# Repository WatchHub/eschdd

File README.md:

BLDC Motor Controller Circuit by youtube user: https://www.youtube.com/channel/UCetsjYU0iBuMPbXi1aA_XXg

Demo: https://www.youtube.com/watch?v=p9SYtOp8aG0

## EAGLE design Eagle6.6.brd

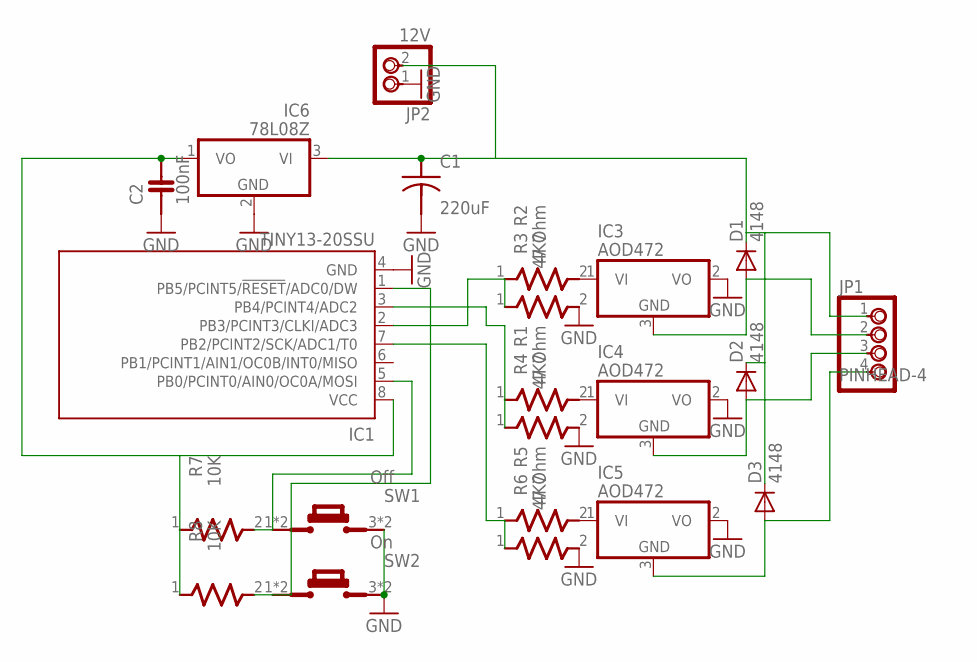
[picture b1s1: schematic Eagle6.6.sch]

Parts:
C1: 220uF; CAP-2,5
C2: 100nF; CAP-NP5
D1, D2, D3: 4148; SMB
IC1: TINY13-20SSU; 8S1
IC3, IC4, IC5: AOD472; TO252
IC6: 78L08Z; TO92
JP1: PINHEAD-4
JP2: 12V; PINHEAD-2
R1, R2, R5: 47 Ohm; R-7,5
R3, R4, R6: 4K7; R-7,5
R7, R8: 10K; R-7,5
SW1: Off; KEY-5
SW2: On; KEY-5

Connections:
GND: C1.- (2), C2.1, IC1.4 (GND), IC3.2 (VO), IC4.2 (VO), IC5.2 (VO), IC6.2 (GND), JP2.1, R3.2, R4.2, R6.2, SW1.3 (2), SW1.4 (2), SW2.3 (2), SW2.4 (2)
unnamed: IC3.1 (VI), R2.2
unnamed: IC4.1 (VI), R1.2
unnamed: IC5.1 (VI), R5.2
unnamed: IC1.7 (PB2/PCINT2/SCK/ADC1/T0), R5.1, R6.1
unnamed: IC1.3 (PB4/PCINT4/ADC2), R1.1, R4.1
unnamed: IC1.2 (PB3/PCINT3/CLKI/ADC3), R2.1, R3.1
unnamed: IC1.5 (PB0/PCINT0/AIN0/OC0A/MOSI), R7.2, SW1.1, SW1.2 (1)
unnamed: D1.A, IC3.3 (GND), JP1.2
unnamed: D2.A, IC4.3 (GND), JP1.3
unnamed: D3.A, IC5.3 (GND), JP1.4
unnamed: C1.+ (1), D1.C, D2.C, D3.C, IC6.3 (VI), JP1.1, JP2.2
unnamed: IC1.1 (PB5/PCINT5/!RESET!/ADC0/DW), R8.2, SW2.1, SW2.2 (1)
unnamed: C2.2, IC1.8 (VCC), IC6.1 (VO), R7.1, R8.1

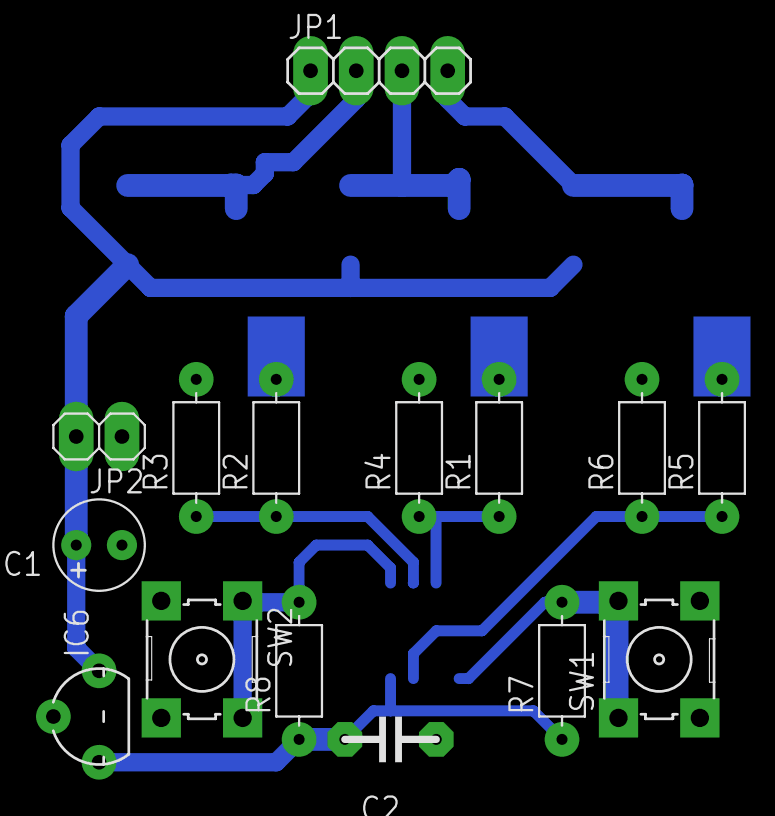
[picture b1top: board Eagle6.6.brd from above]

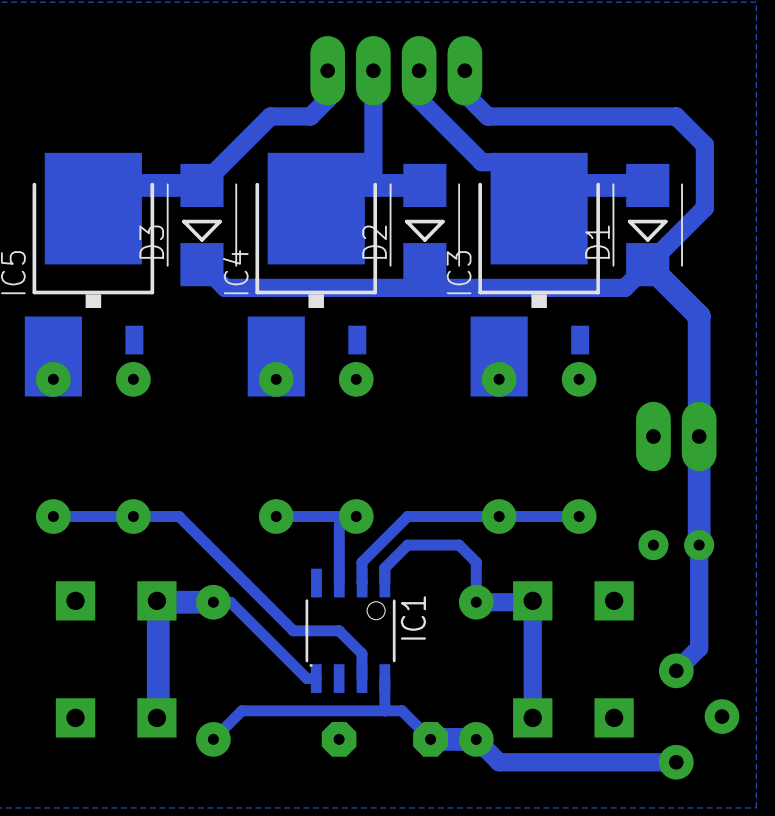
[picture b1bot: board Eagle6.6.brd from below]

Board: 2 copper layers, 22 parts (7 on the bottom side), 14 nets.

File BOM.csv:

"Part";"Value";"Device";"Package";"Description";"MF";"MPN";"OC_FARNELL";"OC_NEWARK";
"C1";"220uF";"CAP-2,5";"CAP-2,5";"";"";"";"";"";
"C2";"100nF";"CAP-NP5";"CAP-NP5";"";"";"";"";"";
"D1";"4148";"DIODE-SMB";"SMB";"DIODE";"";"";"";"";
"D2";"4148";"DIODE-SMB";"SMB";"DIODE";"";"";"";"";
"D3";"4148";"DIODE-SMB";"SMB";"DIODE";"";"";"";"";
"IC1";"TINY13-20SSU";"TINY13-20SSU";"8S1";"8-bit AVR Microcontroller with 1K Bytes In-System Programmable Flash";"";"ATTINY13-20SSU";"1455133";"58M3771";
"IC3";"AOD472";"7805DT";"TO252";"Positive VOLTAGE REGULATOR";"";"";"";"";
"IC4";"AOD472";"7805DT";"TO252";"Positive VOLTAGE REGULATOR";"";"";"";"";
"IC5";"AOD472";"7805DT";"TO252";"Positive VOLTAGE REGULATOR";"";"";"";"";
"IC6";"78L08Z";"78L08Z";"TO92";"Positive VOLTAGE REGULATOR";"";"";"";"";
"JP1";"PINHEAD-4";"PINHEAD-4";"PINHEAD-4";"";"";"";"";"";
"JP2";"12V";"PINHEAD-2";"PINHEAD-2";"";"";"";"";"";
"R1";"47 Ohm";"R-7,5";"R-7,5";"";"";"";"";"";
"R2";"47 Ohm";"R-7,5";"R-7,5";"";"";"";"";"";
"R3";"4K7";"R-7,5";"R-7,5";"";"";"";"";"";
"R4";"4K7";"R-7,5";"R-7,5";"";"";"";"";"";
"R5";"47 Ohm";"R-7,5";"R-7,5";"";"";"";"";"";
"R6";"4K7";"R-7,5";"R-7,5";"";"";"";"";"";
"R7";"10K";"R-7,5";"R-7,5";"";"";"";"";"";
"R8";"10K";"R-7,5";"R-7,5";"";"";"";"";"";
"SW1";"Off";"KEY-5";"KEY-5";"";"";"";"";"";
"SW2";"On";"KEY-5";"KEY-5";"";"";"";"";"";

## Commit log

2020-10-26 Added BOM and png version of schematic
